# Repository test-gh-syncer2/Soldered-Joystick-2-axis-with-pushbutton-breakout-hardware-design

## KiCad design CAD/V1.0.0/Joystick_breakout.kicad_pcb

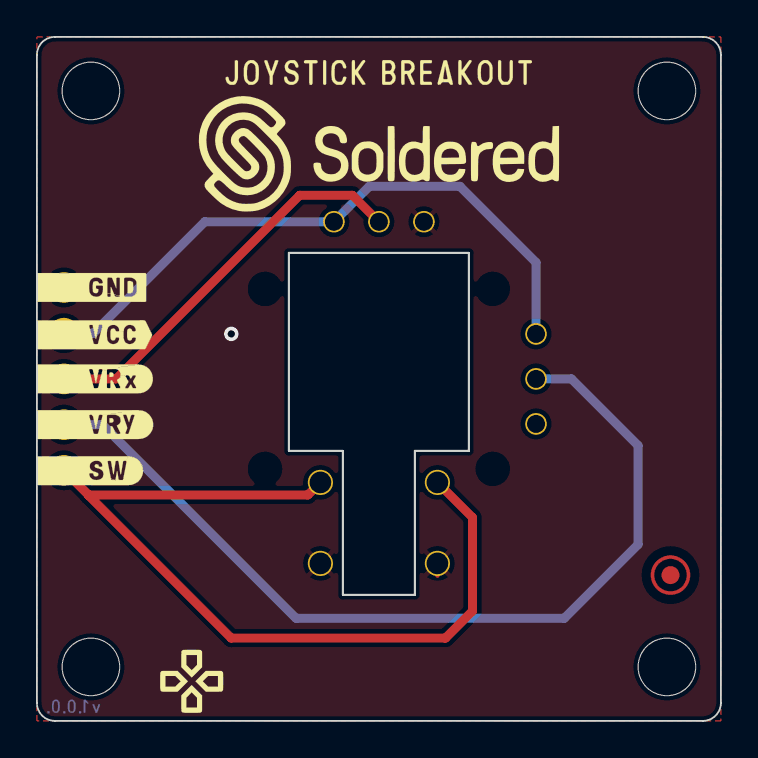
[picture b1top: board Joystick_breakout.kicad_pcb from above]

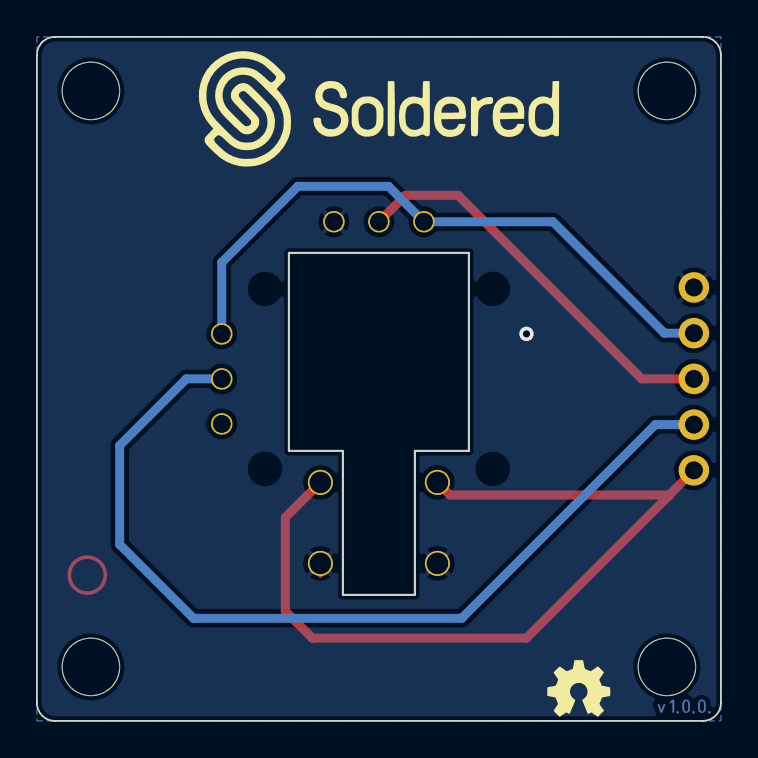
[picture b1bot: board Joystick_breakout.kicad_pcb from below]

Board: 2 copper layers, 38.0 x 38.0 mm, 8 parts (2 on the bottom side), 5 nets.

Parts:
FD1: FIDUCIAL; FIDUCIAL_23
H1, H2, H3, H4: HOLE_3.2mm
K1: Joystick; joystick
K2: HEADER_MALE_5X1
Ref**: Val**; Version1.0.0.

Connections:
GND: K1.1, K1.6, K2.5
SW: K1.2, K2.1
VCC: K1.5, K1.8, K2.4
VRx: K1.7, K2.3
VRy: K1.4, K2.2

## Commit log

2021-09-23 Syncing to git
2021-09-23 Updating open source files.
